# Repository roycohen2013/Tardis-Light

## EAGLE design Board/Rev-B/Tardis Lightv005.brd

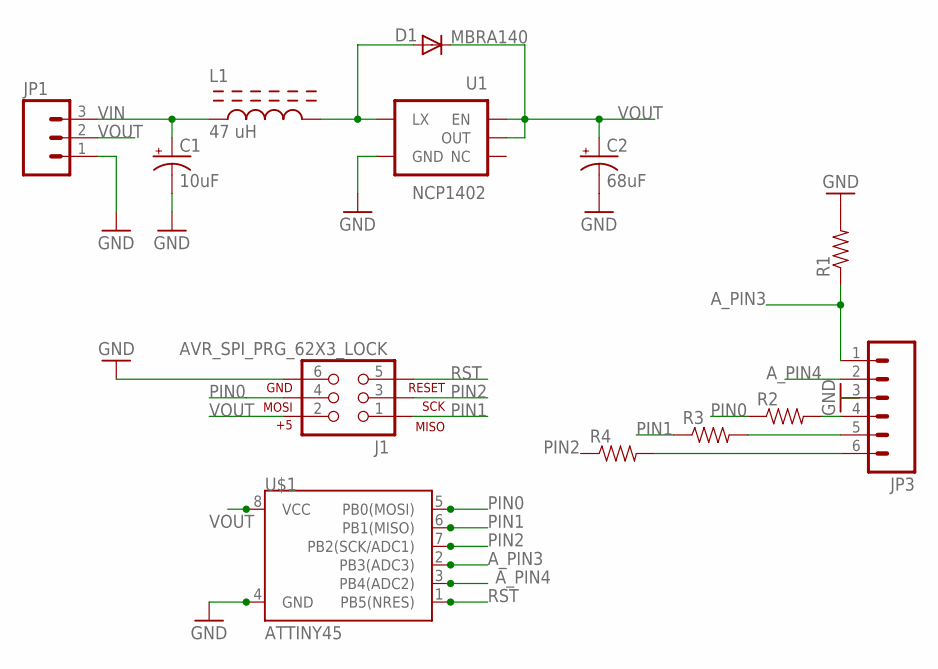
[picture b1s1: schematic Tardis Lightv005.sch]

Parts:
C1: 10uF; EIA3216
C2: 68uF; EIA2917
D1: MBRA140; SMA-DIODE
J1: AVR_SPI_PRG_62X3_LOCK; 2X3_LOCK
JP1: M03PTH; 1X03
JP3: M06SIP; 1X06
L1: 47 uH; NR6028
R1, R2, R3, R4: RESISTOR1206; 1206
U1: NCP1402; SOT23-5
U$1: ATTINY45; SO08-EIAJ

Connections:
A_PIN3: JP3.1, R1.1, U$1.2 (PB3(ADC3))
A_PIN4: JP3.2, U$1.3 (PB4(ADC2))
GND: C1.C (-), C2.C (-), J1.6, JP1.1, JP3.3, R1.2, U1.4 (GND), U$1.4 (GND)
unnamed: JP3.4, R2.2
unnamed: D1.A, L1.P$2 (P2), U1.5 (LX)
unnamed: JP3.5, R3.2
unnamed: JP3.6, R4.2
PIN0: J1.4, R2.1, U$1.5 (PB0(MOSI))
PIN1: J1.1, R3.1, U$1.6 (PB1(MISO))
PIN2: J1.3, R4.1, U$1.7 (PB2(SCK/ADC1))
RST: J1.5, U$1.1 (PB5(NRES))
VIN: C1.A (+), JP1.3, L1.P$1 (P1)
VOUT: C2.A (+), D1.C, J1.2, JP1.2, U1.1 (EN), U1.2 (OUT), U$1.8 (VCC)

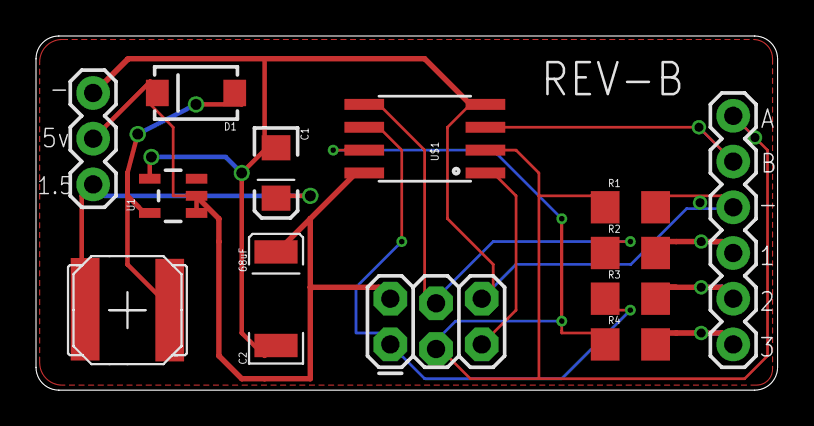
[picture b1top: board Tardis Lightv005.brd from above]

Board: 2 copper layers, 41.2 x 19.7 mm, 13 parts (0 on the bottom side), 13 nets.

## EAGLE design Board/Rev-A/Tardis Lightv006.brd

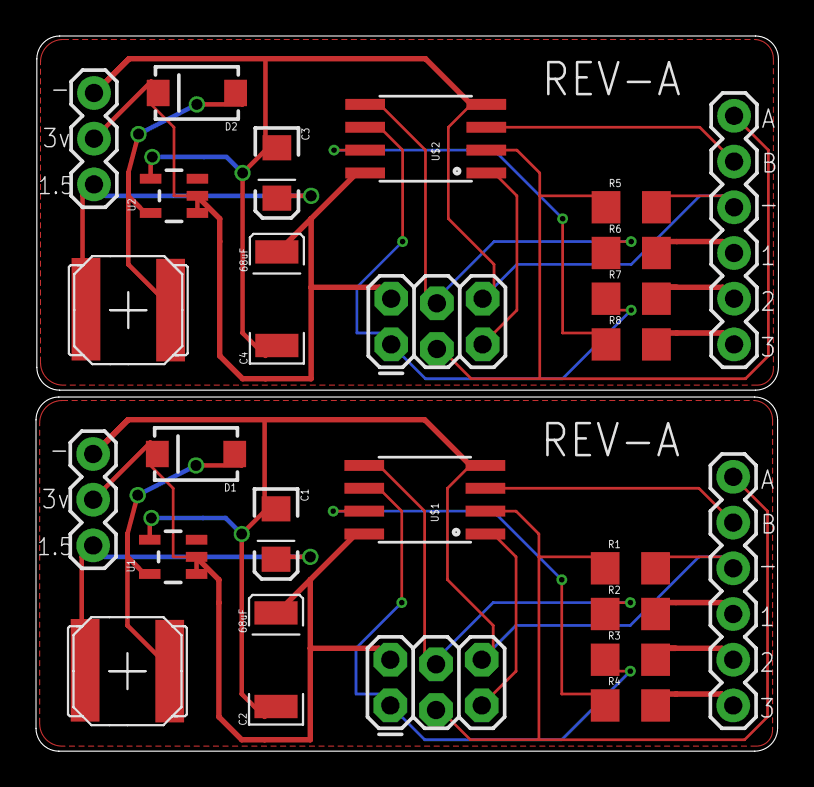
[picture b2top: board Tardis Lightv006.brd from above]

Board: 2 copper layers, 41.2 x 39.7 mm, 26 parts (0 on the bottom side), 26 nets.

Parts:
C1, C3: 10uF; EIA3216
C2, C4: 68uF; EIA2917
D1, D2: MBRA140; SMA-DIODE
J1, J2: AVR_SPI_PRG_62X3_LOCK; 2X3_LOCK
JP1, JP2: 1X03
JP3, JP4: 1X06
L1, L2: 47 uH; NR6028
R1, R2, R3, R4, R5, R6, R7, R8: 1206
U1, U2: NCP1402; SOT23-5
U$1, U$2: ATTINY45; SO08-EIAJ

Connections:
A_PIN1: J2.3, JP4.1, R5.1, U$2.2
A_PIN2: JP4.2, U$2.3
A_PIN3: J1.3, JP3.1, R1.1, U$1.2
A_PIN4: JP3.2, U$1.3
GND: C1.C, C2.C, J1.6, JP1.1, JP3.3, R1.2, U1.4, U$1.4
GND1: C3.C, C4.C, J2.6, JP2.1, JP4.3, R5.2, U2.4, U$2.4
unnamed: JP3.4, R2.2
unnamed: D2.A, L2.P$2, U2.5
unnamed: D1.A, L1.P$2, U1.5
unnamed: JP4.4, R6.2
unnamed: JP3.5, R3.2
unnamed: JP3.6, R4.2
unnamed: JP4.5, R7.2
unnamed: JP4.6, R8.2
PIN0: J1.4, R2.1, U$1.5
PIN1: J1.1, R3.1, U$1.6
PIN2: R4.1, U$1.7
PIN3: J2.4, R6.1, U$2.5
PIN4: J2.1, R7.1, U$2.6
PIN5: R8.1, U$2.7
RST: J1.5, U$1.1
RST1: J2.5, U$2.1
VIN: C1.A, JP1.3, L1.P$1
VIN1: C3.A, JP2.3, L2.P$1
VOUT: C2.A, D1.C, J1.2, JP1.2, U1.1, U1.2, U$1.8
VOUT1: C4.A, D2.C, J2.2, JP2.2, U2.1, U2.2, U$2.8

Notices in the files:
parts and their libraries:
SparkFun: Licensing: CC v3.0 Share-Alike You are welcome to use this library for commercial purposes.
